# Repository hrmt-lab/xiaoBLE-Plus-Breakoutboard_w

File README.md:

# xiaoBLE-Plus-Breakoutboard
xiaoBLE-Plus Breakoutboard

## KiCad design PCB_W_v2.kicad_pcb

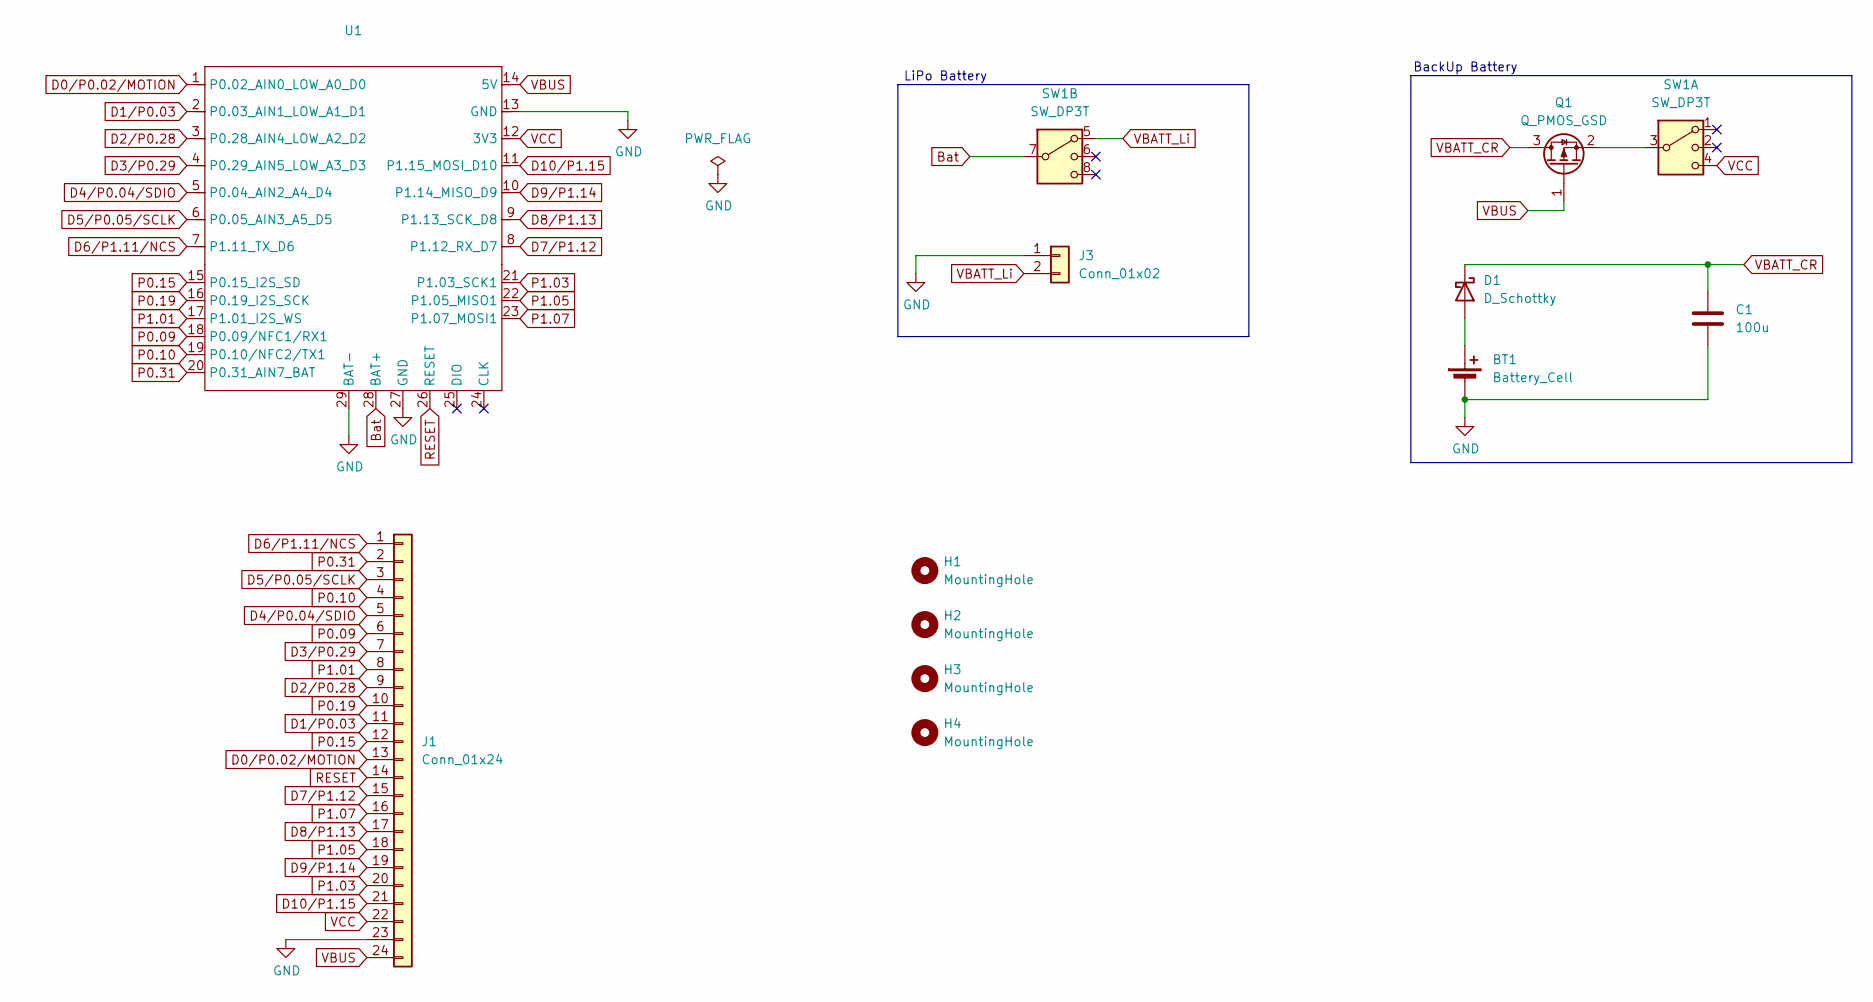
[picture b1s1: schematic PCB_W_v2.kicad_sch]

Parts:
BT1: Battery_Cell; BatteryHolder_Multicomp_BC-2001_1x2032
C1: 100u; C_1206_3216Metric_Pad1.33x1.80mm_HandSolder
D1: D_Schottky; D_SOD-123
H1, H2, H3, H4: MountingHole; m2_Screw_Hole
J1: Conn_01x24; Hirose_FH12-24S-0.5SH_1x24-1MP_P0.50mm_Horizontal
J3: Conn_01x02; JST_PH_S2B-PH-K_1x02_P2.00mm_Horizontal
Q1: Q_PMOS_GSD; SOT-23-3
SW1: SW_DP3T; EG2315
U1: Xiao-ble-plus-tht

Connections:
Bat: SW1.7, U1.28 (BAT+)
D0/P0.02/MOTION: J1.13, U1.1 (P0.02_AIN0_LOW_A0_D0)
D1/P0.03: J1.11, U1.2 (P0.03_AIN1_LOW_A1_D1)
D2/P0.28: J1.9, U1.3 (P0.28_AIN4_LOW_A2_D2)
D3/P0.29: J1.7, U1.4 (P0.29_AIN5_LOW_A3_D3)
D4/P0.04/SDIO: J1.5, U1.5 (P0.04_AIN2_A4_D4)
D5/P0.05/SCLK: J1.3, U1.6 (P0.05_AIN3_A5_D5)
D6/P1.11/NCS: J1.1, U1.7 (P1.11_TX_D6)
D7/P1.12: J1.15, U1.8 (P1.12_RX_D7)
D8/P1.13: J1.17, U1.9 (P1.13_SCK_D8)
D9/P1.14: J1.19, U1.10 (P1.14_MISO_D9)
D10/P1.15: J1.21, U1.11 (P1.15_MOSI_D10)
GND: BT1.2 (-), C1.2, J1.23, J3.1, U1.13 (GND), U1.27 (GND), U1.29 (BAT-)
unnamed: BT1.1 (+), D1.2 (A)
unnamed: Q1.2 (S), SW1.3
P0.09: J1.6, U1.18 (P0.09/NFC1/RX1)
P0.10: J1.4, U1.19 (P0.10/NFC2/TX1)
P0.15: J1.12, U1.15 (P0.15_I2S_SD)
P0.19: J1.10, U1.16 (P0.19_I2S_SCK)
P0.31: J1.2, U1.20 (P0.31_AIN7_BAT)
P1.01: J1.8, U1.17 (P1.01_I2S_WS)
P1.03: J1.20, U1.21 (P1.03_SCK1)
P1.05: J1.18, U1.22 (P1.05_MISO1)
P1.07: J1.16, U1.23 (P1.07_MOSI1)
RESET: J1.14, U1.26 (RESET)
VBATT_CR: C1.1, D1.1 (K), Q1.3 (D)
VBATT_Li: J3.2, SW1.5
VBUS: J1.24, Q1.1 (G), U1.14 (5V)
VCC: J1.22, SW1.4, U1.12 (3V3)

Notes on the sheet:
BackUp Battery
LiPo Battery

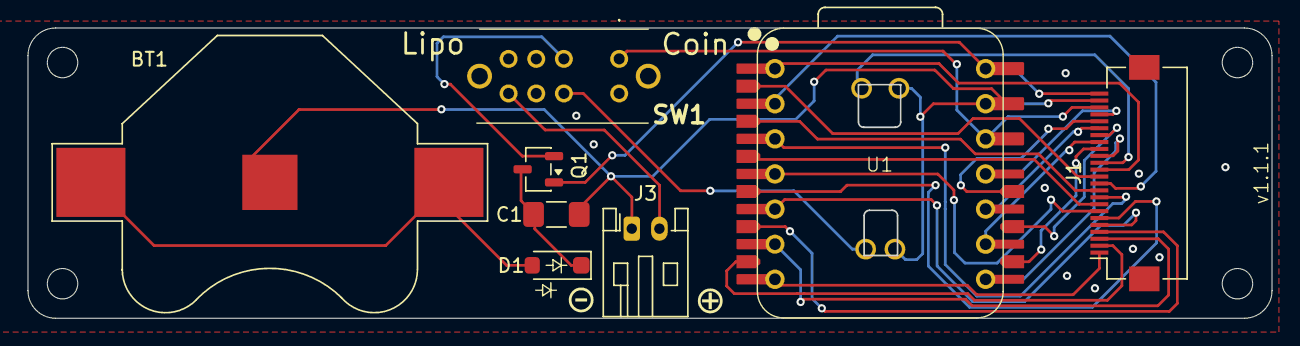
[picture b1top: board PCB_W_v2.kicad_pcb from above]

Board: 2 copper layers, 89.9 x 20.9 mm, 12 parts (0 on the bottom side), 29 nets.

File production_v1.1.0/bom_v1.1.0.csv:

Designator,Footprint,Quantity,Value,LCSC Part #
BT1,BatteryHolder_Multicomp_BC-2001_1x2032,1,Battery_Cell,
C1,1206,1,100u,
D1,D_SOD-123,1,D_Schottky,
J1,Hirose_FH12-24S-0.5SH_1x24-1MP_P0.50mm_Horizontal,1,Conn_01x24,C262669
J3,JST_PH_S2B-PH-K_1x02_P2.00mm_Horizontal,1,Conn_01x02,
Q1,SOT-23-3,1,Q_PMOS_GSD,
SW1,EG2315,1,SW_DP3T,
U1,Xiao-ble-plus-tht,1,~,

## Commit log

2026-03-01 Add image to README for xiaoBLE-Plus Breakoutboard
